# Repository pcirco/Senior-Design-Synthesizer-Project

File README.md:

# Senior-Design-Synthesizer-Project
## Paul Circo 
### University of Nebraska-Lincoln Electrical Engineering Class of 2021

This repository contains the code written by Paul Circo for his senior design project in which his group built a synthesizer.  This repository also contains the group's course report, as well as the KiCad files that were created by Paul Circo for the design of one of the PCBs used in the project.

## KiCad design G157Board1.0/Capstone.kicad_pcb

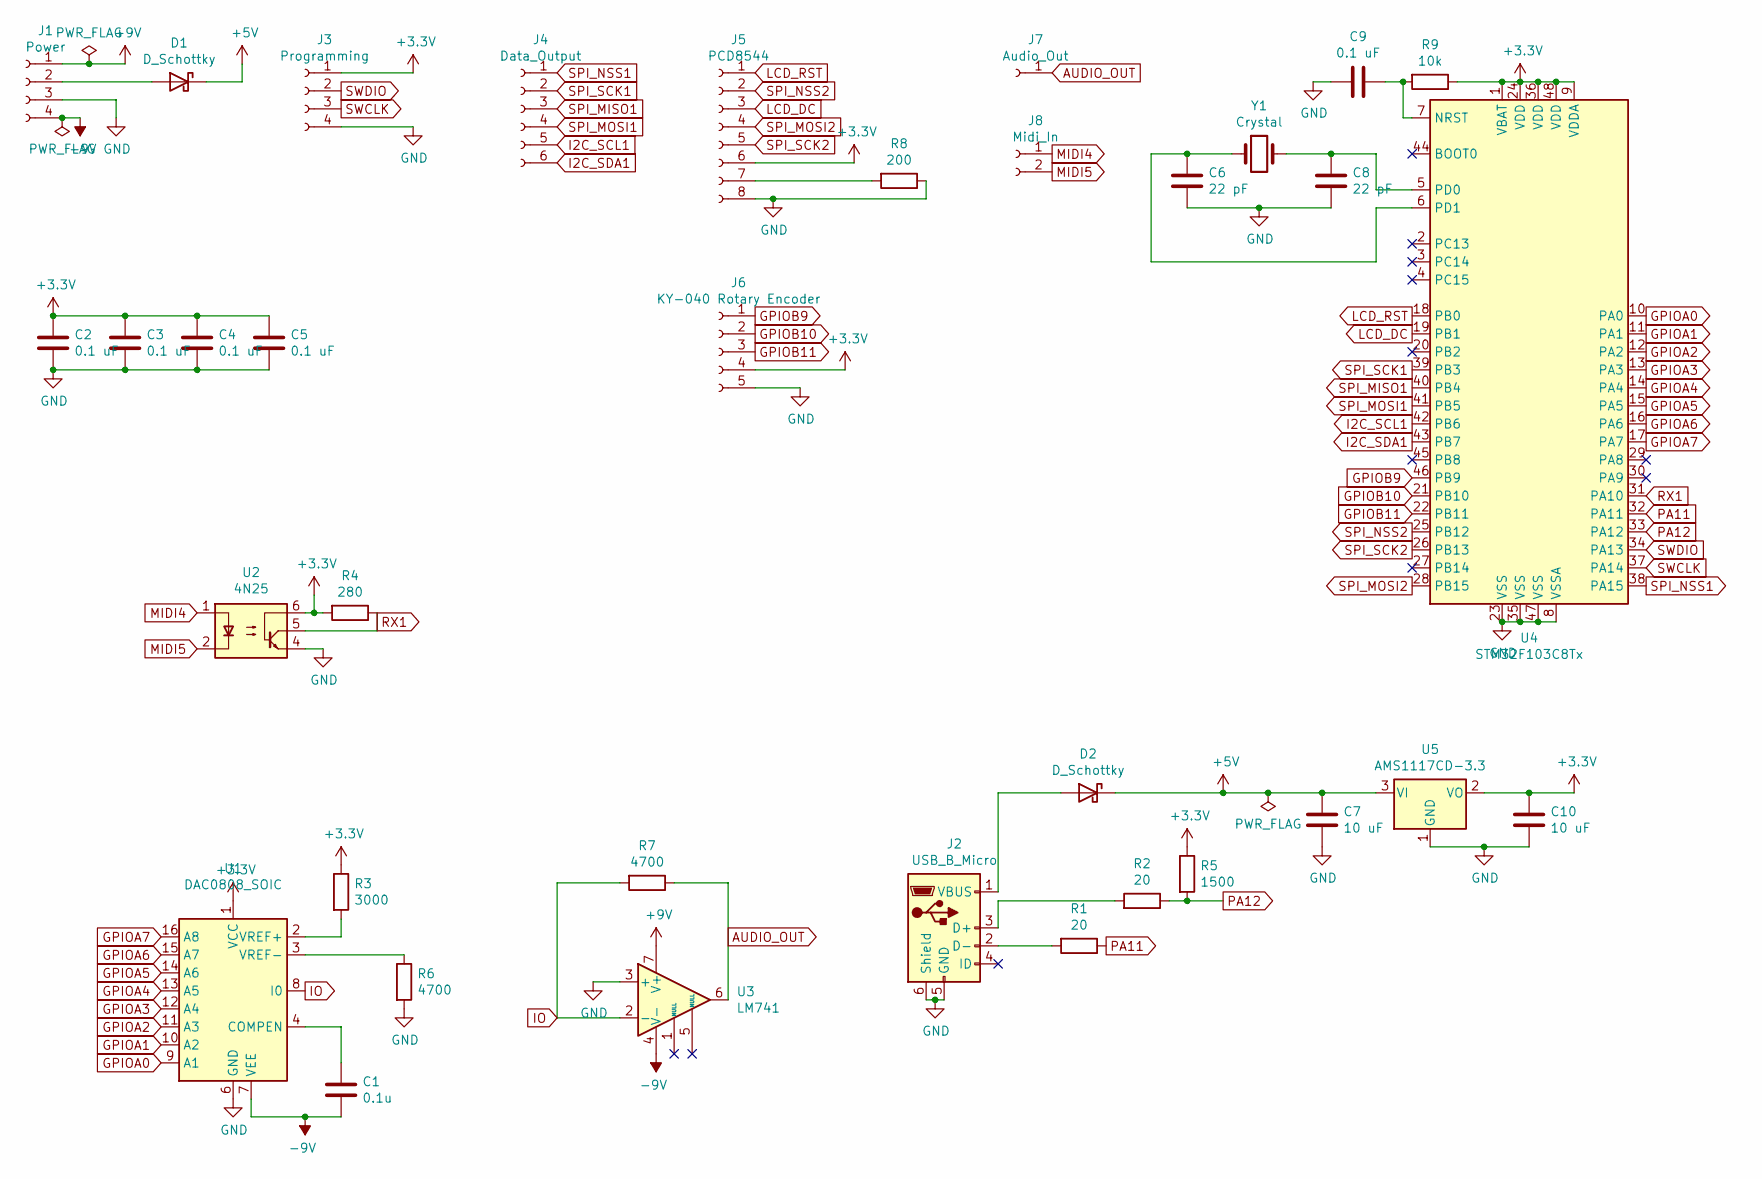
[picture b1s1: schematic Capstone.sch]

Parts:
C1: 0.1u; C_0805_2012Metric
C2, C3, C4, C5, C9: 0.1 uF; C_0805_2012Metric
C6, C8: 22 pF; C_0805_2012Metric
C7, C10: 10 uF; C_0805_2012Metric
D1, D2: D_Schottky; D_1206_3216Metric
J1: Power; PinHeader_1x04_P2.54mm_Vertical
J2: USB_B_Micro; USB_Micro-B_Molex_47346-0001
J3: Programming; PinHeader_1x04_P2.54mm_Vertical
J4: Data_Output; PinHeader_1x06_P2.54mm_Vertical
J5: PCD8544; PinHeader_1x08_P2.54mm_Vertical
J6: KY-040 Rotary Encoder; PinHeader_1x05_P2.54mm_Vertical
J7: Audio_Out; PinHeader_1x01_P2.54mm_Vertical
J8: Midi_In; PinHeader_1x02_P2.54mm_Vertical
R1, R2: 20; R_0805_2012Metric
R3: 3000; R_0805_2012Metric
R4: 280; R_0805_2012Metric
R5: 1500; R_0805_2012Metric
R6, R7: 4700; R_0805_2012Metric
R8: 200; R_0805_2012Metric
R9: 10k; R_0805_2012Metric
U1: DAC0808_SOIC; SOIC-16_3.9x9.9mm_P1.27mm
U2: 4N25; DIP-6_W7.62mm
U3: LM741; DIP-8_W10.16mm
U4: STM32F103C8Tx; LQFP-48_7x7mm_P0.5mm
U5: AMS1117CD-3.3; TO-252-3_TabPin2
Y1: Crystal; Crystal_SMD_5032-2Pin_5.0x3.2mm

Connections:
+3V3: C2.1, C3.1, C4.1, C5.1, C10.1, J3.1, J5.6, J6.4, R3.1, R4.2, R5.1, R9.1, U1.1 (VCC), U2.6, U4.1 (VBAT), U4.9 (VDDA), U4.24 (VDD), U4.36 (VDD), U4.48 (VDD), U5.2 (VO)
+5V: C7.1, D1.1 (K), D2.1 (K), U5.3 (VI)
+9V: J1.1, U3.7 (V+)
-9V: C1.2, J1.4, U1.7 (VEE), U3.4 (V-)
AUDIO_OUT: J7.1, R7.1, U3.6
GND: C2.2, C3.2, C4.2, C5.2, C6.2, C7.2, C8.2, C9.2, C10.2, J1.3, J2.5 (GND), J2.6 (Shield), J3.4, J5.8, J6.5, R6.2, R8.1, U1.6 (GND), U2.4, U3.3 (+), U4.8 (VSSA), U4.23 (VSS), U4.35 (VSS), U4.47 (VSS), U5.1 (GND)
GPIOA0: U1.9 (A1), U4.10 (PA0)
GPIOA1: U1.10 (A2), U4.11 (PA1)
GPIOA2: U1.11 (A3), U4.12 (PA2)
GPIOA3: U1.12 (A4), U4.13 (PA3)
GPIOA4: U1.13 (A5), U4.14 (PA4)
GPIOA5: U1.14 (A6), U4.15 (PA5)
GPIOA6: U1.15 (A7), U4.16 (PA6)
GPIOA7: U1.16 (A8), U4.17 (PA7)
GPIOB9: J6.1, U4.46 (PB9)
GPIOB10: J6.2, U4.21 (PB10)
GPIOB11: J6.3, U4.22 (PB11)
I2C_SCL1: J4.5, U4.42 (PB6)
I2C_SDA1: J4.6, U4.43 (PB7)
IO: R7.2, U1.8 (I0), U3.2 (-)
LCD_DC: J5.3, U4.19 (PB1)
LCD_RST: J5.1, U4.18 (PB0)
MIDI4: J8.1, U2.1
MIDI5: J8.2, U2.2
unnamed: C1.1, U1.4 (COMPEN)
unnamed: C6.1, U4.6 (PD1), Y1.1
unnamed: C8.1, U4.5 (PD0), Y1.2
unnamed: C9.1, R9.2, U4.7 (NRST)
unnamed: D1.2 (A), J1.2
unnamed: D2.2 (A), J2.1 (VBUS)
unnamed: J2.2 (D-), R1.2
unnamed: J2.3 (D+), R2.2
unnamed: J5.7, R8.2
unnamed: R3.2, U1.2 (VREF+)
unnamed: R6.1, U1.3 (VREF-)
PA11: R1.1, U4.32 (PA11)
PA12: R2.1, R5.2, U4.33 (PA12)
RX1: R4.1, U2.5, U4.31 (PA10)
SPI_MISO1: J4.3, U4.40 (PB4)
SPI_MOSI1: J4.4, U4.41 (PB5)
SPI_MOSI2: J5.4, U4.28 (PB15)
SPI_NSS1: J4.1, U4.38 (PA15)
SPI_NSS2: J5.2, U4.25 (PB12)
SPI_SCK1: J4.2, U4.39 (PB3)
SPI_SCK2: J5.5, U4.26 (PB13)
SWCLK: J3.3, U4.37 (PA14)
SWDIO: J3.2, U4.34 (PA13)

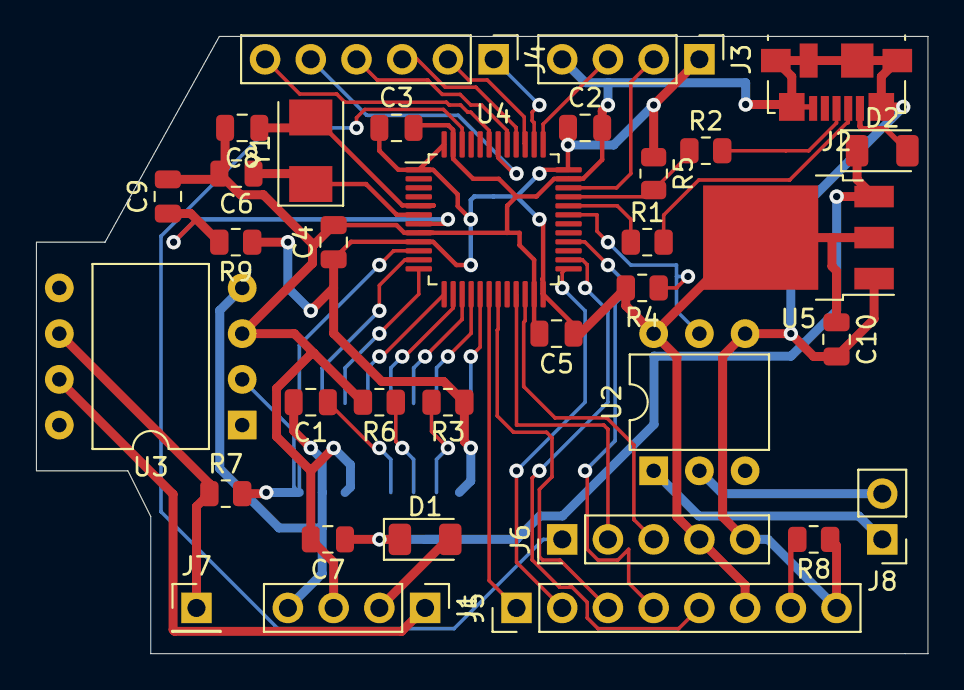
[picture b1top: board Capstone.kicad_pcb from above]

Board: 2 copper layers, 49.5 x 34.3 mm, 35 parts (1 on the bottom side), 47 nets.

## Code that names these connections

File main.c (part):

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  GPIO_InitStruct.Pull = GPIO_NOPULL;
  HAL_GPIO_Init(GPIOC, &GPIO_InitStruct);

  /*Configure GPIO pins : PA0 PA1 PA2 PA3
                           PA4 PA5 PA6 PA7 */
  GPIO_InitStruct.Pin = GPIO_PIN_0|GPIO_PIN_1|GPIO_PIN_2|GPIO_PIN_3
                          |GPIO_PIN_4|GPIO_PIN_5|GPIO_PIN_6|GPIO_PIN_7;
  GPIO_InitStruct.Mode = GPIO_MODE_OUTPUT_PP;
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  GPIO_InitStruct.Speed = GPIO_SPEED_FREQ_HIGH;
  HAL_GPIO_Init(GPIOA, &GPIO_InitStruct);

  /*Configure GPIO pins : PB0 PB1 */
  GPIO_InitStruct.Pin = GPIO_PIN_0|GPIO_PIN_1;
  GPIO_InitStruct.Mode = GPIO_MODE_OUTPUT_PP;
  GPIO_InitStruct.Pull = GPIO_NOPULL;
  GPIO_InitStruct.Speed = GPIO_SPEED_FREQ_LOW;
  HAL_GPIO_Init(GPIOB, &GPIO_InitStruct);

  /*Configure GPIO pin : PB10 */
  GPIO_InitStruct.Pin = GPIO_PIN_10;
  GPIO_InitStruct.Mode = GPIO_MODE_INPUT;
  GPIO_InitStruct.Pull = GPIO_NOPULL;
  HAL_GPIO_Init(GPIOB, &GPIO_InitStruct);

  /*Configure GPIO pin : PB11 */
  GPIO_InitStruct.Pin = GPIO_PIN_11;
  GPIO_InitStruct.Mode = GPIO_MODE_INPUT;
  GPIO_InitStruct.Pull = GPIO_NOPULL;
  HAL_GPIO_Init(GPIOB, &GPIO_InitStruct);

  /*Configure GPIO pin : PA10 */
  GPIO_InitStruct.Pin = GPIO_PIN_10;
  GPIO_InitStruct.Mode = GPIO_MODE_INPUT;
  GPIO_InitStruct.Pull = GPIO_NOPULL;
  HAL_GPIO_Init(GPIOA, &GPIO_InitStruct);

  /*Configure GPIO pin : PA15 */
  GPIO_InitStruct.Pin = GPIO_PIN_15;
  GPIO_InitStruct.Mode = GPIO_MODE_INPUT;
  GPIO_InitStruct.Pull = GPIO_PULLDOWN;
  HAL_GPIO_Init(GPIOA, &GPIO_InitStruct);

  /*Configure GPIO pins : PB3 PB4 PB5 */
  GPIO_InitStruct.Pin = GPIO_PIN_3|GPIO_PIN_4|GPIO_PIN_5;
  GPIO_InitStruct.Mode = GPIO_MODE_INPUT;
  GPIO_InitStruct.Pull = GPIO_PULLDOWN;
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

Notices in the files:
main.c:
© Copyright (c) 2021 STMicroelectronics.
All rights reserved.
This software component is licensed by ST under BSD 3-Clause license,
the "License"; You may not use this file except in compliance with the
License. You may obtain a copy of the License at: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
(C) COPYRIGHT STMicroelectronics *****END OF FILE
